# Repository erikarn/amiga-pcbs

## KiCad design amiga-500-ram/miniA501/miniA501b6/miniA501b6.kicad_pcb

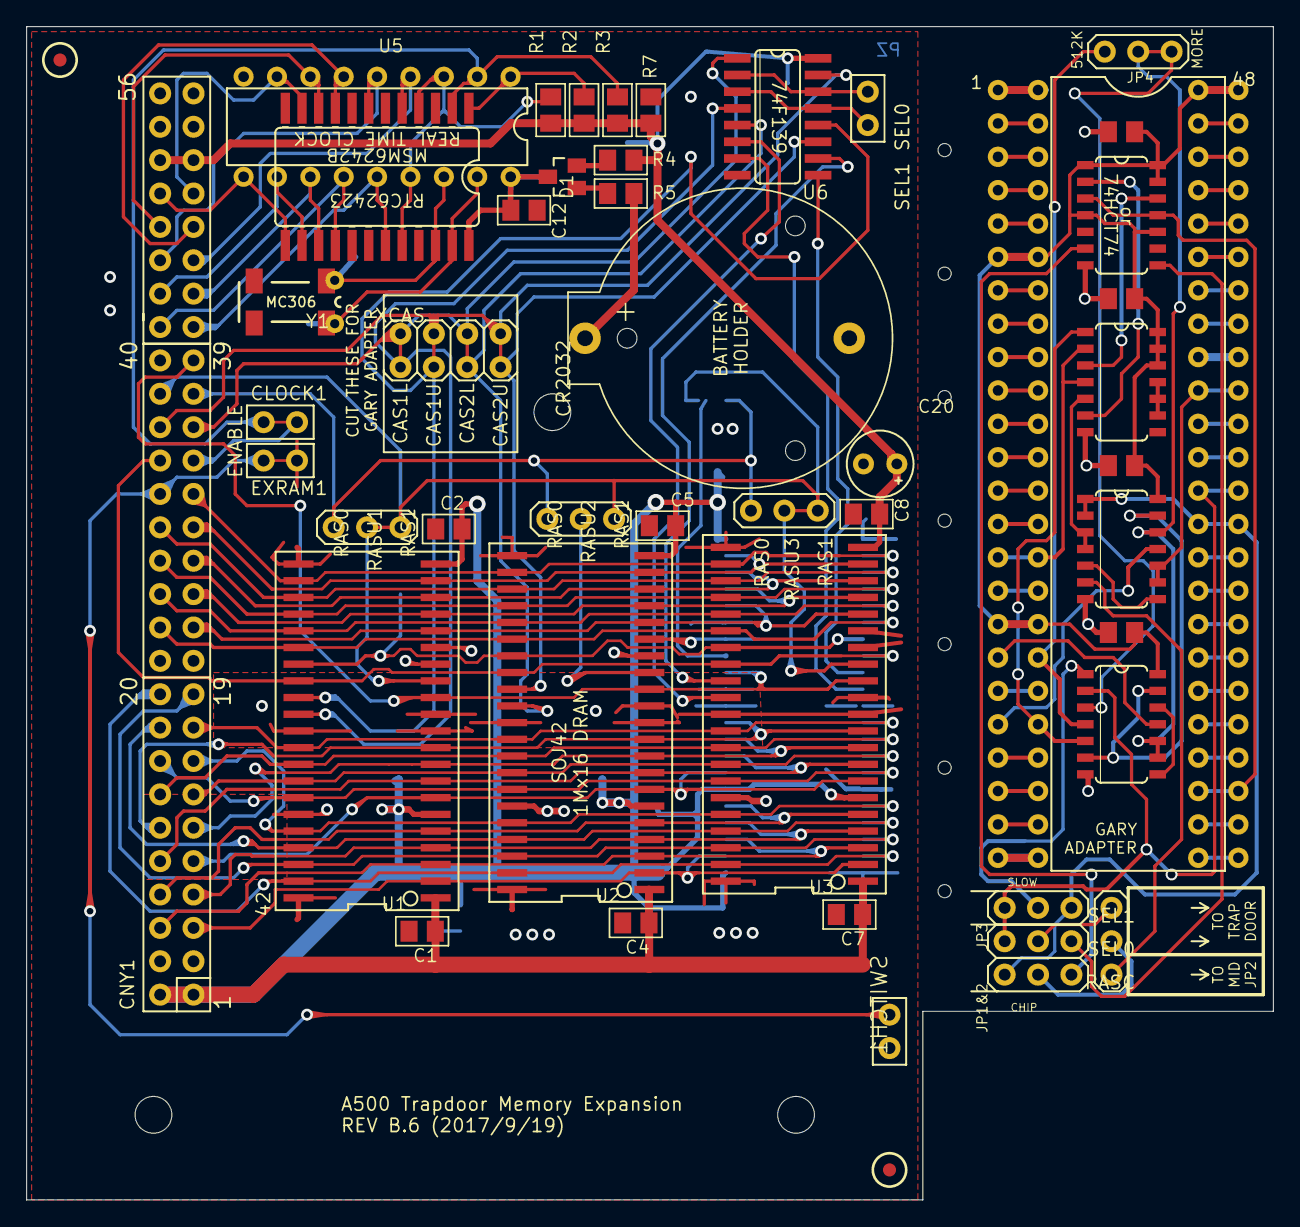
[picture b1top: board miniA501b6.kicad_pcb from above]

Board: 2 copper layers, 94.9 x 89.3 mm, 78 parts (0 on the bottom side), 129 nets.

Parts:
@HOLE0, @HOLE1, @HOLE2, @HOLE3, @HOLE4, @HOLE5, @HOLE6, @HOLE7, @HOLE8, @HOLE9: (no value)
A9: SJ
BAT1: CR2032THM; CR2032-THRU
C1, C2, C3, C4, C5, C6, C7, C8, C12, C16, C21, C22, C23: 100nF; C0805KPZ
C9, C17, C18, C24: 100n; C0805K
C11: TANT; C1206PZ
C13: 4.7uF 10V; C0805KPZ
C14, C15: 22pF; C0805KPZ
C19: C-US; C1206PZ
C20: CPOL-EUE2.5-5; E2,5-5
CLOCK1: PINHD-1X2; 1X02
CNY1: PINHD-2X20; 2X20
CNY2: PINHD-2X8; 2X08
D1: BAT721C; SOT23
EXRAM1: PINHD-1X2; 1X02
GARY1: DIL48
IC1, IC2, IC3: 74F00; SO14
IC4: 74F74; SO14
J8: PINHD-1X3; 1X03
JP1, JP2, JP5, JP6, JP7, JP8, JP9: PINHD-1X3; 1X03
JP3, JP4: PINHD-1X1; 1X01
JP10: PINHD-2X4; 2X04
LED1: LED; M0805PZ
R1, R2, R3: 10K; M0805PZ
R4, R5: 470; M0805PZ
R6: 1K; M0805PZ
R7: 100K; C0805KPZ
SEL[0_1]1: PINHD-1X2; 1X02
SJ1: SJ2W; SJ_2
SOCKET(MOBO)1: DIL48
SWITCH1: PINHD-1X2; 1X02
U1, U2, U3, U4: DRAMSOJ40A; SOJ40
U5: OKI MSM6242B; DIL18
U6: 74F139D; SO16
U55: RTC72421SOP24; SOP24
U$1, U$2: FIDUCIAL; FIDUCIAL_1MM
Y1: MC-306

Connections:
//A19: IC2.3, IC2.4, IC3.5
//A19_FF: IC4.6, JP2.3
//BLIT: GARY1.15, IC3.2, IC3.4, SOCKET(MOBO)1.15
//GARY_RAMEN: GARY1.20, IC1.5, IC3.1
//GARY_RAMEN_FF: IC4.8, JP6.3
//GARY_REGEN: GARY1.18, IC1.4, JP9.3
//NEW_RAMEN: IC2.11, SOCKET(MOBO)1.20
//NEW_REGEN: IC1.11, SOCKET(MOBO)1.18
/A0: CNY1.23, U1.17, U2.17, U3.17, U4.17
/A1: CNY1.25, U1.18, U2.18, U3.18, U4.18
/A2: CNY1.27, U1.19, U2.19, U3.19, U4.19
/A3: CNY1.29, U1.20, U2.20, U3.20, U4.20
/A4: CNY1.31, U1.23, U2.23, U3.23, U4.23
/A5: CNY1.30, U1.24, U2.24, U3.24, U4.24
/A6: CNY1.28, U1.25, U2.25, U3.25, U4.25
/A7: CNY1.26, U1.26, U2.26, U3.26, U4.26
/A8: CNY1.24, U1.27, U2.27, U3.27, U4.27
/A9: A9.2, U1.28, U2.28, U3.28, U4.28
/A19: SEL[0_1]1.1, U6.2, U6.14
/A20: SEL[0_1]1.2, U6.3, U6.13
/A23: GARY1.39, IC2.9, IC2.10, SOCKET(MOBO)1.39
/ALE: R1.P$1, U5.3, U5.15, U55.4, U55.20
/CASL_U1: JP10.8, U1.31, U6.4
/CASL_U2: JP10.4, U2.31, U6.5
/CASL_U3: U3.31, U6.6
/CASL_U4: U4.31, U6.7
/CASU_U1: JP10.6, U1.30, U6.12
/CASU_U2: JP10.2, U2.30, U6.11
/CASU_U3: U3.30, U6.10
/CASU_U4: U4.30, U6.9
/CCKQ: GARY1.27, IC4.3, IC4.11, SOCKET(MOBO)1.27
/CS0: CLOCK1.1, R3.P$1, U5.2, U55.2
/D0: CNY1.5, U1.2, U2.2, U3.2, U4.2
/D1: CNY1.6, U1.3, U2.3, U3.3, U4.3
/D2: CNY1.7, U1.4, U2.4, U3.4, U4.4
/D3: CNY1.8, U1.5, U2.5, U3.5, U4.5
/D4: CNY1.9, U1.7, U2.7, U3.7, U4.7
/D5: CNY1.10, U1.8, U2.8, U3.8, U4.8
/D6: CNY1.11, U1.9, U2.9, U3.9, U4.9
/D7: CNY1.12, U1.10, U2.10, U3.10, U4.10
/D8: CNY1.17, U1.33, U2.33, U3.33, U4.33
/D9: CNY1.14, U1.34, U2.34, U3.34, U4.34
/D10: CNY1.13, U1.35, U2.35, U3.35, U4.35
/D11: CNY1.16, U1.36, U2.36, U3.36, U4.36
/D12: CNY1.15, U1.38, U2.38, U3.38, U4.38
/D13: CNY1.18, U1.39, U2.39, U3.39, U4.39
/D14: CNY1.19, U1.40, U2.40, U3.40, U4.40
/D15: CNY1.20, U1.41, U2.41, U3.41, U4.41
/ENABLE: CNY1.32, EXRAM1.1, SWITCH1.1
/OE: CNY1.34, U1.29, U2.29, U3.29, U4.29
/ORIGA19: GARY1.35, IC2.1, IC2.2, JP2.1, JP8.1, SOCKET(MOBO)1.35
/ORIGA20: GARY1.36, IC1.2, JP6.1, JP8.3, SOCKET(MOBO)1.36
/P2: GARY1.2, SOCKET(MOBO)1.2
/P3: GARY1.3, SOCKET(MOBO)1.3
/P4: GARY1.4, SOCKET(MOBO)1.4
/P5: GARY1.5, SOCKET(MOBO)1.5
/P7: GARY1.7, SOCKET(MOBO)1.7
/P8: GARY1.8, SOCKET(MOBO)1.8
/P9: GARY1.9, SOCKET(MOBO)1.9
/P10: GARY1.10, SOCKET(MOBO)1.10
/P11: GARY1.11, SOCKET(MOBO)1.11
/P12: GARY1.12, SOCKET(MOBO)1.12
/P13: GARY1.13, SOCKET(MOBO)1.13
/P14: GARY1.14, SOCKET(MOBO)1.14
/P16: GARY1.16, SOCKET(MOBO)1.16
/P19: GARY1.19, SOCKET(MOBO)1.19
/P21: GARY1.21, SOCKET(MOBO)1.21
/P22: GARY1.22, SOCKET(MOBO)1.22
/P23: GARY1.23, SOCKET(MOBO)1.23
/RAS0: CNY1.37, JP1.1, JP5.1, JP7.1, SJ1.1
/RAS1: CNY1.38, JP1.3, JP5.3, JP7.3, SJ1.3
/RASU1: JP1.2, U1.14
/RASU2: JP7.2, U2.14
/RASU3: JP5.2, U3.14
/RASU4: SJ1.2, U4.14
/RAS_CTL: IC2.6, J8.1
/SEL0: J8.2, JP2.2
/SEL1: J8.3, JP6.2
/STD.P: R2.P$1, U5.1, U55.1
/VBAT: C12.P$2, C13.P$1, C19.P$1, D1.3, U5.18, U55.24
/WE: CNY1.39, U1.13, U2.13, U3.13, U4.13
/XA2: CNY2.5, U5.4, U55.5
/XA3: CNY2.6, U5.5, U55.7
/XA4: CNY2.7, U5.6, U55.9
/XA5: CNY2.8, U5.7, U55.10
/XCASL: CNY1.35, JP10.3, JP10.7, U6.1
/XCASU: CNY1.36, JP10.1, JP10.5, U6.15
/XCLKCS: CLOCK1.2, CNY1.33
/XCLKRD: CNY2.9, U5.8, U55.11
/XCLKWR: CNY2.10, U5.10, U55.13
/XD0: CNY2.1, U5.14, U55.19
/XD1: CNY2.2, U5.13, U55.16
/XD2: CNY2.3, U5.12, U55.15
/XD3: CNY2.4, U5.11, U55.14
/XT1: C14.P$1, JP3.1, U5.17, U55.23, Y1.4
/XT2: C15.P$1, JP4.1, U5.16, U55.22, Y1.1
GND: A9.1, BAT1.-, C1.P$1, C2.P$1, C3.P$1, C4.P$1, C5.P$1, C6.P$1, C7.P$1, C8.P$1, C9.2, C11.P$2, C12.P$1, C13.P$2, C14.P$2, C15.P$2, C16.P$2, C17.2, C18.2, C19.P$2, C20.-, C21.P$1, C22.P$1, C23.P$1, C24.2, CNY1.3, CNY1.4, CNY1.21, CNY1.22, CNY2.13, CNY2.14, EXRAM1.2, GARY1.1, GARY1.24, GARY1.40, IC1.7, IC2.7, IC3.7, IC4.7, LED1.P$1, R7.P$2, SOCKET(MOBO)1.1, SOCKET(MOBO)1.24, SOCKET(MOBO)1.40, SWITCH1.2, U1.11, U1.12, U1.15, U1.16, U1.22, U1.32, U1.37, U1.42, U2.11, U2.12, U2.15, U2.16, U2.22, U2.32, U2.37, U2.42, U3.11, U3.12, U3.15, U3.16, U3.22, U3.32, U3.37, U3.42, U4.11, U4.12, U4.15, U4.16, U4.22, U4.32, U4.37, U4.42, U5.9, U6.8, U55.12
unnamed: BAT1.+, R5.P$2
unnamed: D1.1, R5.P$1
unnamed: D1.2, R4.P$1
unnamed: GARY1.25, SOCKET(MOBO)1.25
unnamed: GARY1.26, SOCKET(MOBO)1.26
unnamed: GARY1.28, SOCKET(MOBO)1.28
unnamed: GARY1.29, SOCKET(MOBO)1.29
unnamed: GARY1.30, SOCKET(MOBO)1.30
unnamed: GARY1.31, SOCKET(MOBO)1.31
unnamed: GARY1.32, SOCKET(MOBO)1.32
unnamed: GARY1.33, SOCKET(MOBO)1.33
unnamed: GARY1.34, SOCKET(MOBO)1.34
unnamed: GARY1.37, SOCKET(MOBO)1.37
unnamed: GARY1.38, SOCKET(MOBO)1.38
unnamed: GARY1.41, SOCKET(MOBO)1.41
unnamed: GARY1.42, SOCKET(MOBO)1.42
unnamed: GARY1.43, SOCKET(MOBO)1.43
unnamed: GARY1.44, SOCKET(MOBO)1.44
unnamed: GARY1.45, SOCKET(MOBO)1.45
unnamed: GARY1.46, SOCKET(MOBO)1.46
unnamed: GARY1.47, SOCKET(MOBO)1.47
unnamed: IC1.1, JP8.2
unnamed: IC1.3, JP9.1
unnamed: IC1.9, IC1.10, IC2.12, JP9.2
unnamed: IC1.8, IC1.12
unnamed: IC1.6, IC1.13, IC2.13
unnamed: IC2.5, IC2.8
unnamed: IC3.3, IC4.12
unnamed: IC3.6, IC4.2
unnamed: IC3.9, IC3.10, IC3.11
unnamed: LED1.P$2, R6.P$1
VCC: C1.P$2, C2.P$2, C3.P$2, C4.P$2, C5.P$2, C6.P$2, C7.P$2, C8.P$2, C9.1, C11.P$1, C16.P$1, C17.1, C18.1, C20.+, C21.P$2, C22.P$2, C23.P$2, C24.1, CNY1.1, CNY1.2, CNY2.11, CNY2.12, GARY1.6, GARY1.17, GARY1.48, IC1.14, IC2.14, IC3.12, IC3.13, IC3.14, IC4.1, IC4.4, IC4.10, IC4.13, IC4.14, R1.P$2, R2.P$2, R3.P$2, R4.P$2, R6.P$2, R7.P$1, SOCKET(MOBO)1.6, SOCKET(MOBO)1.17, SOCKET(MOBO)1.48, U1.1, U1.6, U1.21, U2.1, U2.6, U2.21, U3.1, U3.6, U3.21, U4.1, U4.6, U4.21, U6.16

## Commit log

2022-01-16 Add the amiga 500 gary RAm adapter project from peteAU and others on the amiga forum.
    This one is a bit special - I've deleted the RAM adapter itself as I just want the
    Gary adapter board so I can look at adapting an existing A501 adapter. We'll see
    how well that works!
2022-01-16 dd the converted project over too, now that I have it converted with the pcb and schematic.
2022-01-30 add pdf
2022-01-31 Add a very good summary of what to set the jumpers to!
